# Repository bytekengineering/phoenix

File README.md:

# bytek phoenix

La tarjeta **bytek phoenix** es una placa electrónica open hardware especialmente diseñada para aprender a programar construyendo robots. Sabiendo la importancia del IoT en el siglo XXI, esta solución provista de un NodeMCU es la mejor opción para introducirse en este mundo. ¡Conecta tus creaciones a Internet! http://bytek.info/phoenix

## Web oficial
[bytek.info](http://bytek.info/)
## Wiki
 - [Información de interés](https://github.com/bytekengineering/phoenix/wiki)
 - [Tutorial: Cómo configurar Arduino](https://github.com/bytekengineering/phoenix/wiki/Tutorial:-C%C3%B3mo-configurar-Arduino)
## Licencia
  
[Creative Commons - Attribution - Share Alike](http://creativecommons.org/licenses/by-sa/4.0/)

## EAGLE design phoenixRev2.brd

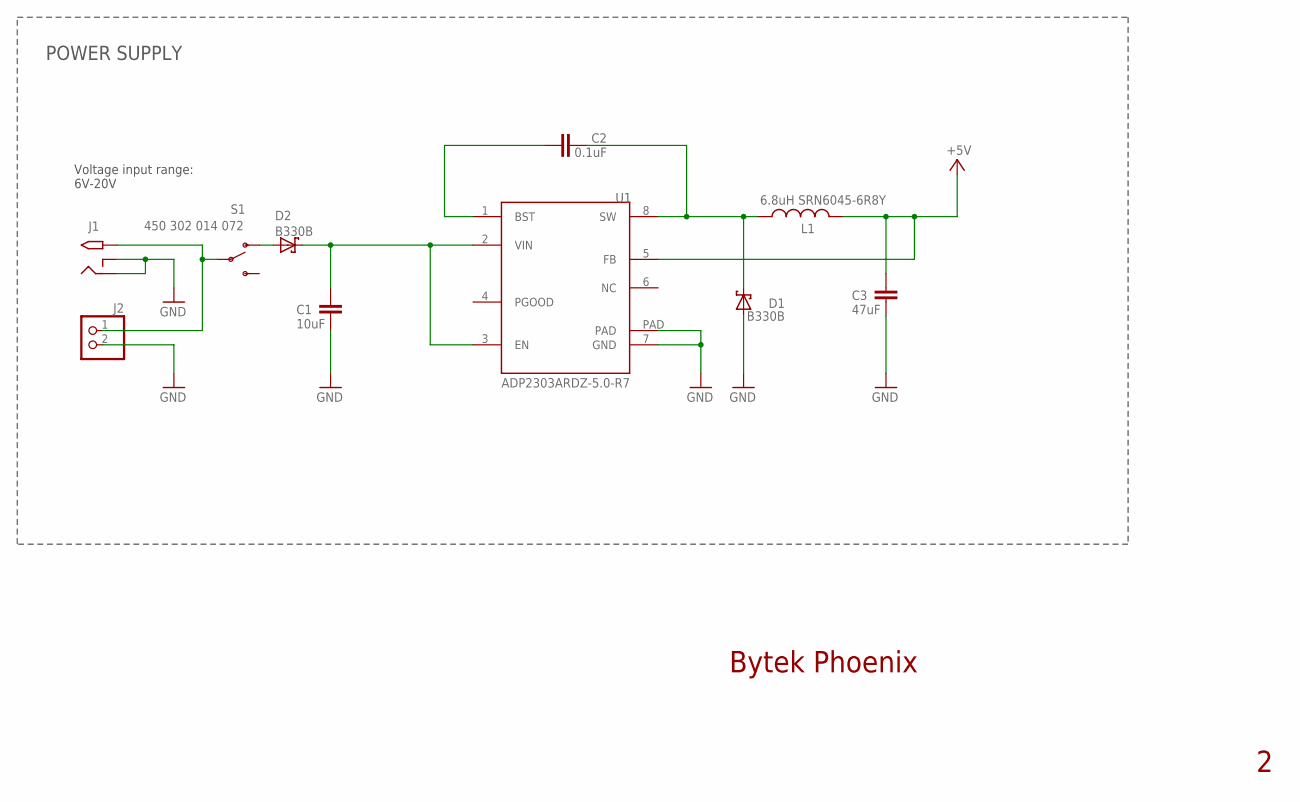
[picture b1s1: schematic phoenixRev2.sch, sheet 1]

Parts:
C1: 10uF; C0805
C2: 0.1uF; C0805
C3: 47uF; C1206
D1, D2: B330B; SMB
J1: 2.1MMJACKTHM; PJ-102A
J2: PINHD-1X2; 1X02
L1: 6.8uH SRN6045-6R8Y; POWER-CHOKE_WE-TPC
S1: 450 302 014 072; SWITCH_SPDT_PTH_11.6X4.0MM
U1: ADP2303ARDZ-5.0-R7; SO08_PAD

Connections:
+5V: C3.1, L1.2, U1.5 (FB); also elsewhere on the board
GND: C1.2, C3.2, D1.A, J1.RING, J1.RING_SW, J2.2, U1.7 (GND), U1.PAD; also elsewhere on the board
unnamed: D2.A, S1.1 (O)
unnamed: C2.1, U1.1 (BST)
unnamed: C2.2, D1.C, L1.1, U1.8 (SW)
unnamed: C1.1, D2.C, U1.2 (VIN), U1.3 (EN)
unnamed: J1.TIP, J2.1, S1.2

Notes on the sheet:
POWER SUPPLY
Voltage input range: 6V-20V
Bytek Phoenix

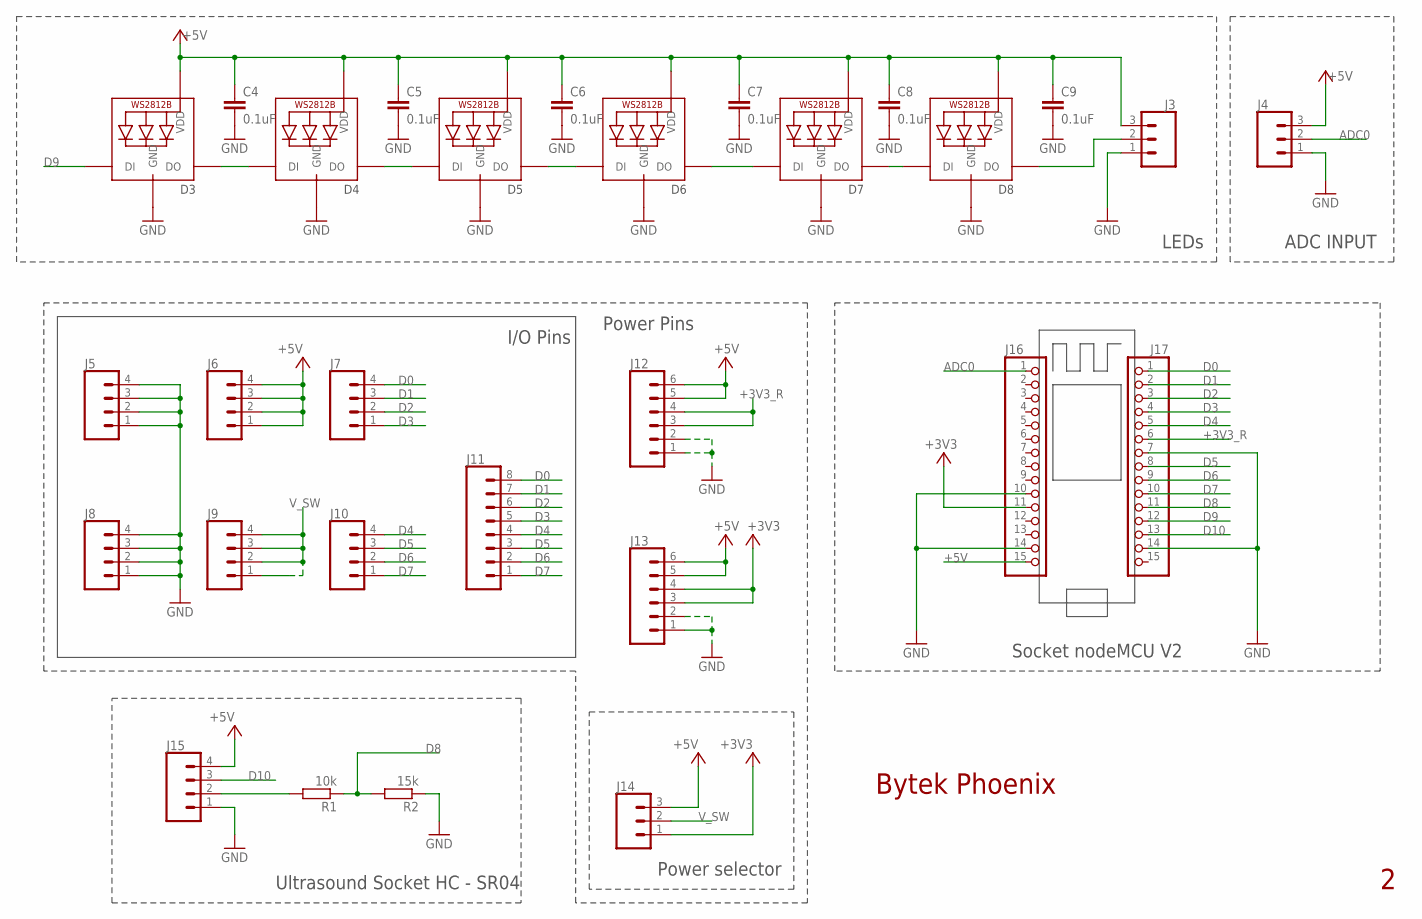
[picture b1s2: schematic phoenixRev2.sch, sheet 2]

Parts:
C4, C5, C6, C7, C8, C9: 0.1uF; C0805
D3, D4, D5, D6, D7, D8: WS2812B5050; WS2812B
J3, J4, J14: CONN_03; 1X03
J5, J6, J7, J8, J9, J10, J15: CONN_04; 1X04
J11: CONN_08"; 1X08
J12, J13: CONN_06SILK_FEMALE_PTH; 1X06
J16, J17: PINHD-1X15-CB; 1X15-CB
R1: 10k; R0805
R2: 15k; R0805

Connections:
+3V3: J13.3, J13.4, J14.1, J16.11
+3V3_R: J12.3, J12.4, J17.6
+5V: C4.1, C5.1, C6.1, C7.1, C8.1, C9.1, D3.1-VDD (VDD), D4.1-VDD (VDD), D5.1-VDD (VDD), D6.1-VDD (VDD), D7.1-VDD (VDD), D8.1-VDD (VDD), J3.3, J4.3, J6.1, J6.2, J6.3, J6.4, J12.5, J12.6, J13.5, J13.6, J14.3, J15.4, J16.15; also elsewhere on the board
ADC0: J4.2, J16.1
D0: J7.4, J11.8, J17.1
D1: J7.3, J11.7, J17.2
D2: J7.2, J11.6, J17.3
D3: J7.1, J11.5, J17.4
D4: J10.4, J11.4, J17.5
D5: J10.3, J11.3, J17.8
D6: J10.2, J11.2, J17.9
D7: J10.1, J11.1, J17.10
D8: J17.11, R1.1, R2.2
D9: D3.4-DIN (DI), J17.12
D10: J15.3, J17.13
GND: C4.2, C5.2, C6.2, C7.2, C8.2, C9.2, D3.3-GND (GND), D4.3-GND (GND), D5.3-GND (GND), D6.3-GND (GND), D7.3-GND (GND), D8.3-GND (GND), J3.1, J4.1, J5.1, J5.2, J5.3, J5.4, J8.1, J8.2, J8.3, J8.4, J12.1, J12.2, J13.1, J13.2, J15.1, J16.10, J16.14, J17.7, J17.14, R2.1; also elsewhere on the board
unnamed: D6.2-DOUT (DO), D7.4-DIN (DI)
unnamed: D7.2-DOUT (DO), D8.4-DIN (DI)
unnamed: D8.2-DOUT (DO), J3.2
unnamed: D3.2-DOUT (DO), D4.4-DIN (DI)
unnamed: D4.2-DOUT (DO), D5.4-DIN (DI)
unnamed: J15.2, R1.2
unnamed: D5.2-DOUT (DO), D6.4-DIN (DI)
V_SW: J9.1, J9.2, J9.3, J9.4, J14.2

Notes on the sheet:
Ultrasound Socket HC - SR04
Socket nodeMCU V2
I/O Pins
Power Pins
LEDs
ADC INPUT
Bytek Phoenix
Power selector

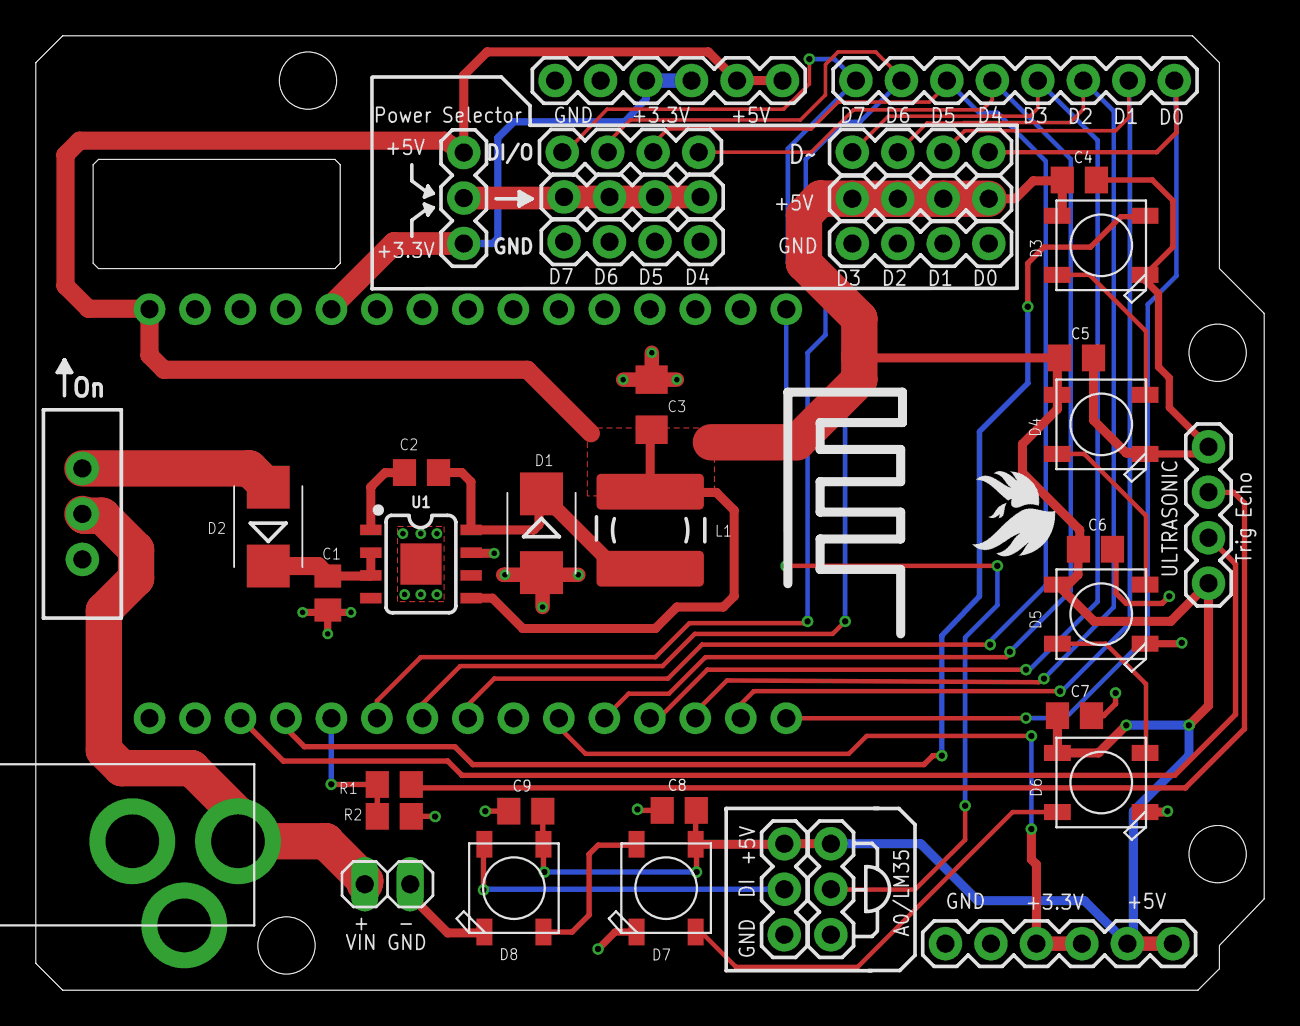
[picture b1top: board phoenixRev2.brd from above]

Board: 2 copper layers, 68.6 x 53.3 mm, 39 parts (0 on the bottom side), 29 nets.

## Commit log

2018-02-08 info added
2018-02-08 tutorial photos uploaded
2018-02-08 new blink gif
2018-02-08 links added
2018-02-27 Example folder added
2018-02-27 Added gif of demo

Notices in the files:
parts and their libraries:
SparkFun-Connectors: Licensing: Creative Commons ShareAlike 4.0 International - https://creativecommons.org/licenses/by-sa/4.0
